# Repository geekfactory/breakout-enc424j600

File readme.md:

# Breakout board for ENC424J600

This board implements a network interface based on the ENC424J600 Ethernet controller from Microchip Technology. All the required components to stablish an Ethernet link are contained in this board.

The signals required to communicate with a host processor are broken out to standard pitch headers. Status leds are provided to show the link and transmission status.

## Features and hardware details

* On-board RJ-45 Jack with magnetics and ethernet controller (MAC and PHY layers)
* Small circuit footprint which fits solderless breadboards
* Requires 3.3 V power supply. No on-board regulation or level shifting provided
* Globally unique MAC address for easy deployment
* Standard header connections for easy prototyping on breadboards and protoboards

## Repository contents

1. __root__ - EAGLE Source files for the board
2. __/documents__ - Additional documentation, datasheets and assembly instructions
3. __/production__ - History of gerber files sent for production
4. __/extras__ - Technical drawings, mounting hardware and related accessories
4. __/firmware__ - Testing or definitive firmware for this board

## Hardware revisions

* 1.0 - First revision

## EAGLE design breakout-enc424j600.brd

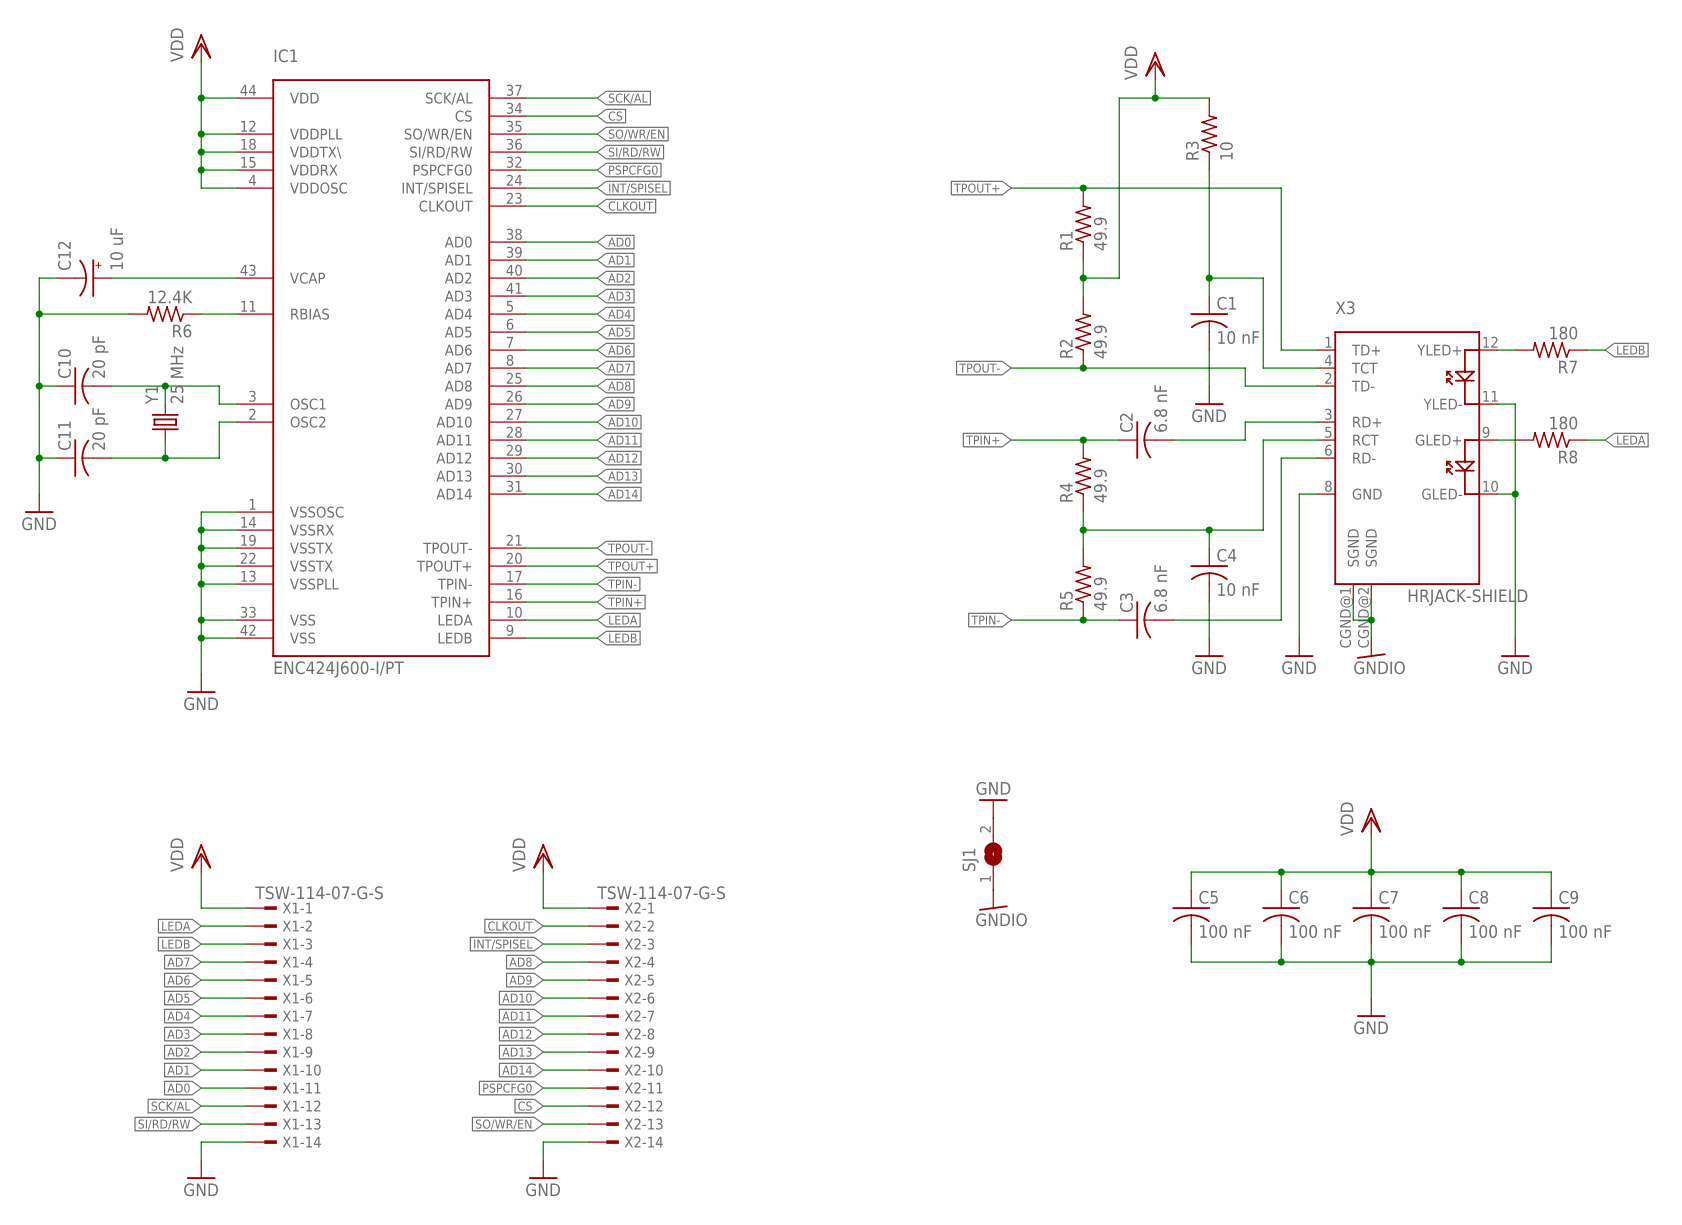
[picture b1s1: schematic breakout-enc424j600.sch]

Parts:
C1, C4: 10 nF; C0805
C2, C3: 6.8 nF; C0805
C5, C6, C7, C8, C9: 100 nF; C0805
C10, C11: 20 pF; C0805
C12: 10 uF; SMC_A
IC1: ENC424J600-I/PT; TQFP44
R1, R2, R4, R5: 49.9; R0805
R3: 10; R0805
R6: 12.4K; R0805
R7, R8: 180; R0805
SJ1: SJW
X1, X2: TSW-114-07-G-S; TSW-114-XX-G-S
X3: HRJACK-SHIELD; HR911105A
Y1: 25 MHz; HC49UP

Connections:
AD0: IC1.38 (AD0), X1.11
AD1: IC1.39 (AD1), X1.10
AD2: IC1.40 (AD2), X1.9
AD3: IC1.41 (AD3), X1.8
AD4: IC1.5 (AD4), X1.7
AD5: IC1.6 (AD5), X1.6
AD6: IC1.7 (AD6), X1.5
AD7: IC1.8 (AD7), X1.4
AD8: IC1.25 (AD8), X2.4
AD9: IC1.26 (AD9), X2.5
AD10: IC1.27 (AD10), X2.6
AD11: IC1.28 (AD11), X2.7
AD12: IC1.29 (AD12), X2.8
AD13: IC1.30 (AD13), X2.9
AD14: IC1.31 (AD14), X2.10
CLKOUT: IC1.23 (CLKOUT), X2.2
CS: IC1.34 (CS), X2.12
GND: C1.2, C4.2, C5.2, C6.2, C7.2, C8.2, C9.2, C10.1, C11.1, C12.-, IC1.1 (VSSOSC), IC1.13 (VSSPLL), IC1.14 (VSSRX), IC1.19 (VSSTX), IC1.22 (VSSTX), IC1.33 (VSS), IC1.42 (VSS), R6.2, SJ1.2, X1.14, X2.14, X3.8 (GND), X3.10 (GLED-), X3.11 (YLED-)
GNDIO: SJ1.1, X3.CGND@1 (SGND), X3.CGND@2 (SGND)
INT/SPISEL: IC1.24 (INT/SPISEL), X2.3
LEDA: IC1.10 (LEDA), R8.1, X1.2
LEDB: IC1.9 (LEDB), R7.1, X1.3
unnamed: C11.2, IC1.2 (OSC2), Y1.1
unnamed: C1.1, R3.1, X3.4 (TCT)
unnamed: C10.2, IC1.3 (OSC1), Y1.2
unnamed: C2.2, X3.3 (RD+)
unnamed: C3.2, X3.6 (RD-)
unnamed: C4.1, R4.1, R5.2, X3.5 (RCT)
unnamed: IC1.11 (RBIAS), R6.1
unnamed: R8.2, X3.9 (GLED+)
unnamed: R7.2, X3.12 (YLED+)
unnamed: C12.+, IC1.43 (VCAP)
PSPCFG0: IC1.32 (PSPCFG0), X2.11
SCK/AL: IC1.37 (SCK/AL), X1.12
SI/RD/RW: IC1.36 (SI/RD/RW), X1.13
SO/WR/EN: IC1.35 (SO/WR/EN), X2.13
TPIN+: C2.1, IC1.16 (TPIN+), R4.2
TPIN-: C3.1, IC1.17 (TPIN-), R5.1
TPOUT+: IC1.20 (TPOUT+), R1.2, X3.1 (TD+)
TPOUT-: IC1.21 (TPOUT-), R2.1, X3.2 (TD-)
VDD: C5.1, C6.1, C7.1, C8.1, C9.1, IC1.4 (VDDOSC), IC1.12 (VDDPLL), IC1.15 (VDDRX), IC1.18 (VDDTX\), IC1.44 (VDD), R1.1, R2.2, R3.2, X1.1, X2.1

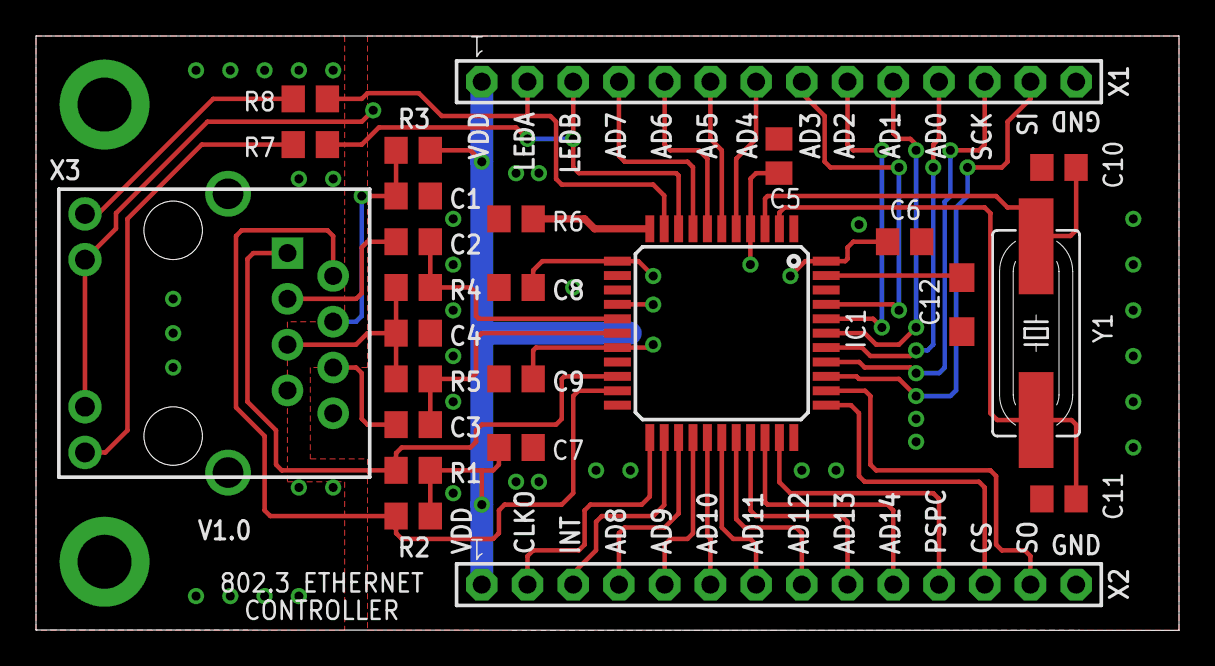
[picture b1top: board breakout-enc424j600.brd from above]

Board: 2 copper layers, 63.5 x 33.0 mm, 26 parts (1 on the bottom side), 41 nets.

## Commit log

2020-04-25 Add pinout on silkscreen, change pin headers, connect ground shield on ethernet, modified board dimension
2021-10-10 Add missing component values
